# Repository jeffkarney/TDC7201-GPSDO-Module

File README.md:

# TDC7201 GPSDO Precision Timing Measurement Module

A standalone **precision timing measurement module** built around the Texas Instruments
**TDC7201** time-to-digital converter.  It measures the phase difference between a
1 PPS (Pulse Per Second) GPS signal and a 10 MHz reference oscillator with sub-nanosecond
resolution, and exposes the results via a REST API served by an **ESP32-C3** WiFi
microcontroller.

> **This is a precision timing measurement module**, not a full GPSDO.  It can be
> integrated into a GPSDO, frequency counter, or any system requiring high-accuracy
> phase comparison.

---

## Features

- **TDC7201** time-to-digital converter – 55 ps resolution per LSB
- **Dual TLV3501** high-speed comparators (2.5 ns propagation delay) for both input channels
- **TL07401** programmable delay line for 12 ns START offset correction
- **ESP32-C3-WROOM-02U-N4** WiFi microcontroller with REST API
- **USB-C** power input (5 V) with USBLC6-2SC6 ESD protection
- **3× SMA connectors** for PPS input, 10 MHz input, and WiFi antenna
- **4-layer PCB** optimised for JLCPCB manufacture (JLC04161H-7628 stack-up)
- **Vue 3 web dashboard** with real-time measurements and uncertainty visualisation
- **Complete REST API** for measurement queries, configuration, and calibration

---

## Specifications

| Parameter                  | Value                           |
|----------------------------|---------------------------------|
| TDC resolution             | 55 ps / LSB                     |
| Combined measurement uncertainty | ±718 ps RMS (95%: ±1.44 ns) |
| Reference input frequency  | 10 MHz (SMA)                    |
| Pulse input                | 1 PPS or any TTL/3.3V edge      |
| Supply voltage             | 5 V USB-C                       |
| Current consumption        | < 200 mA typical                |
| WiFi                       | 802.11 b/g/n 2.4 GHz            |
| Operating temperature      | 0 °C – 50 °C                    |
| PCB dimensions             | 80 mm × 50 mm                   |
| PCB layers                 | 4 (signal / GND / power / signal) |

---

## Repository Structure

```
TDC7201-GPSDO-Module/
├── README.md
├── hardware/
│   ├── BOM.csv                          # Complete BOM with JLCPCB part numbers
│   ├── DESIGN_NOTES.md                  # Design decisions and rationale
│   └── kicad/
│       ├── TDC7201-Module.kicad_sch     # KiCad schematic
│       ├── TDC7201-Module.kicad_pcb     # KiCad PCB layout (4-layer)
│       └── sym-lib-table                # Symbol library table
├── firmware/
│   ├── main/
│   │   ├── main.c                       # Application entry point (ESP-IDF)
│   │   ├── tdc7201_driver.c/h           # TDC7201 SPI/I2C driver
│   │   ├── measurement.c/h              # Phase difference and statistics
│   │   ├── wifi_config.c/h              # WiFi station + HTTP REST server
│   ├── CMakeLists.txt                   # ESP-IDF build configuration
│   └── idf_component.yml               # Component manifest
├── web/
│   ├── src/
│   │   ├── App.vue                      # Main dashboard (Vue 3)
│   │   ├── main.js                      # Application entry point
│   │   ├── components/
│   │   │   ├── MeasurementDisplay.vue   # Real-time measurement display
│   │   │   ├── UncertaintyAnalysis.vue  # Uncertainty breakdown chart
│   │   │   └── ConfigPanel.vue          # Configuration controls
│   │   └── api/
│   │       └── measurements.js          # REST API client
│   ├── public/index.html
│   ├── package.json
│   └── vite.config.js
└── docs/
    ├── API_DOCUMENTATION.md
    ├── CALIBRATION_GUIDE.md
    └── MEASUREMENT_UNCERTAINTY.md
```

---

## Quick Start

### Hardware Setup

1. Connect a **1 PPS** signal (3.3 V TTL, e.g. from a GPS module) to **J1** (SMA)
2. Connect a **10 MHz reference** signal (3.3 V, ≥ 0 dBm) to **J2** (SMA)
3. Connect a **WiFi antenna** to **J3** (SMA) or **J5** (IPX)
4. Apply **5 V USB-C** power via **J4**

### Firmware Build & Flash

Requires [ESP-IDF v5.x](https://docs.espressif.com/projects/esp-idf/en/latest/esp32c3/).

```bash
# Clone and enter firmware directory
cd firmware

# Configure WiFi credentials
idf.py menuconfig  # Set CONFIG_WIFI_SSID and CONFIG_WIFI_PASSWORD

# Build and flash
idf.py -p /dev/ttyUSB0 flash monitor
```

### Web Dashboard

```bash
cd web
npm install
npm run dev       # Development server at http://localhost:3000
npm run build     # Production build in web/dist/
```

Set `VITE_DEV_TARGET=http://<ESP32-IP>` to proxy API calls during development.

---

## REST API Quick Reference

| Method | Endpoint          | Description                     |
|--------|-------------------|---------------------------------|
| GET    | /api/measurements | Current phase difference & uncertainty |
| GET    | /api/stats        | Statistical summary (mean, stddev) |
| GET    | /api/config       | Current configuration           |
| POST   | /api/config       | Apply new configuration         |
| POST   | /api/calibrate    | Reset measurement history       |

See [docs/API_DOCUMENTATION.md](docs/API_DOCUMENTATION.md) for full details.

---

## Integration

This module can be integrated into a GPSDO or other system via:

- **REST API** – query phase difference over WiFi
- **SPI/I2C direct** – bypass the ESP32-C3 and read TDC7201 directly
- **USB-C serial** – debug console at 115200 baud
- **Phase output** – use Δt to drive a PLL/frequency-locking algorithm

---

## Documentation

| Document | Description |
|----------|-------------|
| [hardware/DESIGN_NOTES.md](hardware/DESIGN_NOTES.md) | Design decisions, layout guidelines, calibration |
| [docs/API_DOCUMENTATION.md](docs/API_DOCUMENTATION.md) | Complete REST API reference |
| [docs/CALIBRATION_GUIDE.md](docs/CALIBRATION_GUIDE.md) | Step-by-step calibration procedures |
| [docs/MEASUREMENT_UNCERTAINTY.md](docs/MEASUREMENT_UNCERTAINTY.md) | GUM-compliant uncertainty analysis |

---

## License

MIT License – see [LICENSE](LICENSE) for details.

*Author: jeffkarney*

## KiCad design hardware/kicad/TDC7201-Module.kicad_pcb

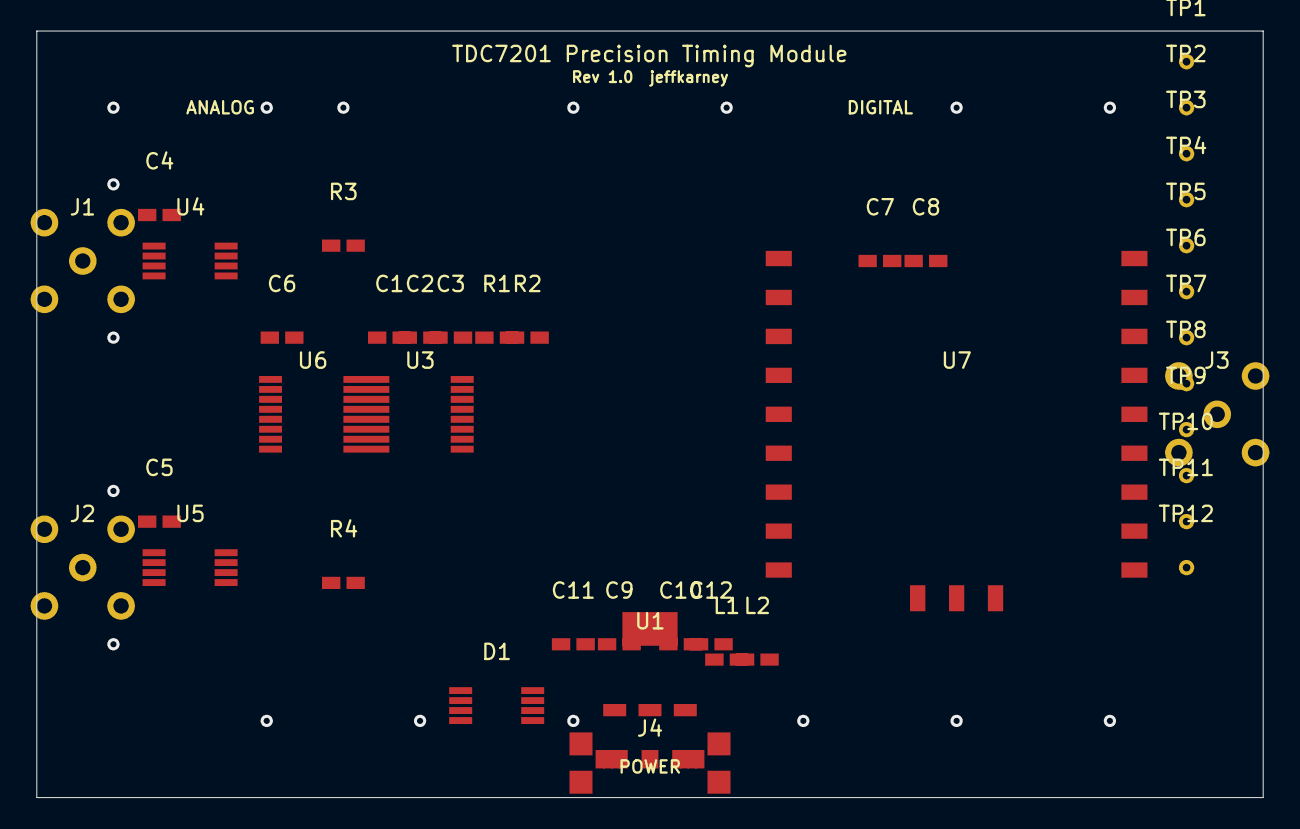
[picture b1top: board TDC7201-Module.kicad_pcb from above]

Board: 4 copper layers, 80.0 x 50.0 mm, 41 parts (0 on the bottom side), 12 nets, no tracks yet.

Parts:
C1, C2, C3, C4, C5, C6, C7, C8, C9, C10: 100nF; C_0603_1608Metric
C11, C12: 10uF; C_0603_1608Metric
D1: USBLC6-2SC6; SOT-23-6
J1: SMA_PPS_IN; SMA_Amphenol_132289_Vertical
J2: SMA_10MHZ_IN; SMA_Amphenol_132289_Vertical
J3: SMA_WiFi_ANT; SMA_Amphenol_132289_Vertical
J4: USB-C; USB_C_Receptacle_GCT_USB4085
L1, L2: Ferrite_600R; L_0805_2012Metric
R1, R2: 10k; R_0603_1608Metric
R3, R4: 47; R_0603_1608Metric
TP1: +5V; TestPoint_THTPad_D1.0mm_Drill0.5mm
TP2: GND; TestPoint_THTPad_D1.0mm_Drill0.5mm
TP3: +3V3; TestPoint_THTPad_D1.0mm_Drill0.5mm
TP4: START; TestPoint_THTPad_D1.0mm_Drill0.5mm
TP5: STOP; TestPoint_THTPad_D1.0mm_Drill0.5mm
TP6: 10MHZ_IN; TestPoint_THTPad_D1.0mm_Drill0.5mm
TP7: SPI_SCK; TestPoint_THTPad_D1.0mm_Drill0.5mm
TP8: SPI_MOSI; TestPoint_THTPad_D1.0mm_Drill0.5mm
TP9: SPI_MISO; TestPoint_THTPad_D1.0mm_Drill0.5mm
TP10: SPI_CS; TestPoint_THTPad_D1.0mm_Drill0.5mm
TP11: PPS_IN; TestPoint_THTPad_D1.0mm_Drill0.5mm
TP12: WiFi_RX; TestPoint_THTPad_D1.0mm_Drill0.5mm
U1: AMS1117-3.3; SOT-223-3_TabPin2
U3: TDC7201; TSSOP-16_4.4x5mm_P0.65mm
U4, U5: TLV3501; TSSOP-8_3x3mm_P0.65mm
U6: TL07401; TSSOP-14_4.4x5mm_P0.65mm
U7: ESP32-C3-WROOM-02U-N4; ESP32-C3-WROOM-02

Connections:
10MHZ_IN: J2.1, TP6.1, U3.4, U5.1
+3V3: C1.1, C2.1, C3.1, C4.1, C5.1, C6.1, C7.1, C8.1, C9.1, C10.1, C12.1, L1.2, L2.2, R1.1, R2.1, TP3.1, U1.3, U3.14, U3.16, U4.8, U5.8, U6.8, U6.14, U7.2
+5V: C11.1, D1.1, D1.3, D1.4, D1.6, J4.A1, J4.A4, J4.B1, J4.B4, L1.1, L2.1, TP1.1, U1.1
GND: C1.2, C2.2, C3.2, C4.2, C5.2, C6.2, C7.2, C8.2, C9.2, C10.2, C11.2, C12.2, D1.2, D1.5, J1.2, J1.3, J1.4, J1.5, J2.2, J2.3, J2.4, J2.5, J3.2, J3.3, J3.4, J3.5, J4.A9, J4.A12, J4.B9, J4.B12, J4.SH1, J4.SH2, J4.SH3, J4.SH4, TP2.1, U1.2, U1.4, U3.12, U3.13, U3.15, U4.2, U4.4, U5.2, U5.4, U6.7, U6.13, U7.1
PPS_IN: J1.1, TP11.1, U4.1
SPI_CS: TP10.1, U3.11, U7.7
SPI_MISO: TP9.1, U3.8, U7.5
SPI_MOSI: TP8.1, U3.10, U7.6
SPI_SCK: TP7.1, U3.9, U7.4
START: R3.1, TP4.1, U3.1, U4.5, U6.1, U6.2
STOP: R4.1, TP5.1, U3.2, U5.5
WiFi_RX: TP12.1, U7.20

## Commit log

2026-04-08 Adding comprehensive README.md for the TDC7201-GPSDO-Module repository.
2026-04-08 Creating detailed design documentation for TDC7201 GPSDO Module
2026-04-08 Create BOM.csv for bill of materials in hardware directory
2026-04-08 Create main.c for ESP32-C3 application with TDC7201 integration
2026-04-08 Add complete TDC7201 driver implementation
2026-04-08 Add App.vue for Vue.js dashboard component in web/src
2026-04-08 Create API documentation for REST endpoints in docs directory
2026-04-08 Adding CALIBRATION_GUIDE.md with step-by-step calibration procedures
2026-04-08 Create TDC7201-GPSDO-Module.kicad_sch with initial components
2026-04-08 Initial plan
2026-04-08 Add complete TDC7201 module design: firmware, hardware, web UI, and documentation
    Agent-Logs-Url: https://github.com/jeffkarney/TDC7201-GPSDO-Module/sessions/d61ec5e3-8d5e-48d1-b7b2-7d299acfeca4
2026-04-08 Update PCB file to valid KiCad 7.0 format
2026-04-08 Regenerate valid KiCad 7.0 PCB and schematic files
    - TDC7201-Module.kicad_pcb: complete rewrite with valid KiCad 7.0
    S-expression syntax (version 20221018). Removes all ;; comments,
    invalid (module ...) / (capacitor ...) / (inductor ...) syntax.
    Adds proper (net 0..15) declarations with numeric IDs, valid
    (footprint ...) blocks for all ICs/connectors with numeric net
    references in pads and vias, 4-layer stackup (F.Cu/In1.Cu/In2.Cu/B.Cu),
2026-04-08 Fix ferrite bead pad net assignments (L1/L2: +5V→+3V3)
    Agent-Logs-Url: https://github.com/jeffkarney/TDC7201-GPSDO-Module/sessions/249e8e96-76a3-4c3b-a7cb-0897e226d90f
